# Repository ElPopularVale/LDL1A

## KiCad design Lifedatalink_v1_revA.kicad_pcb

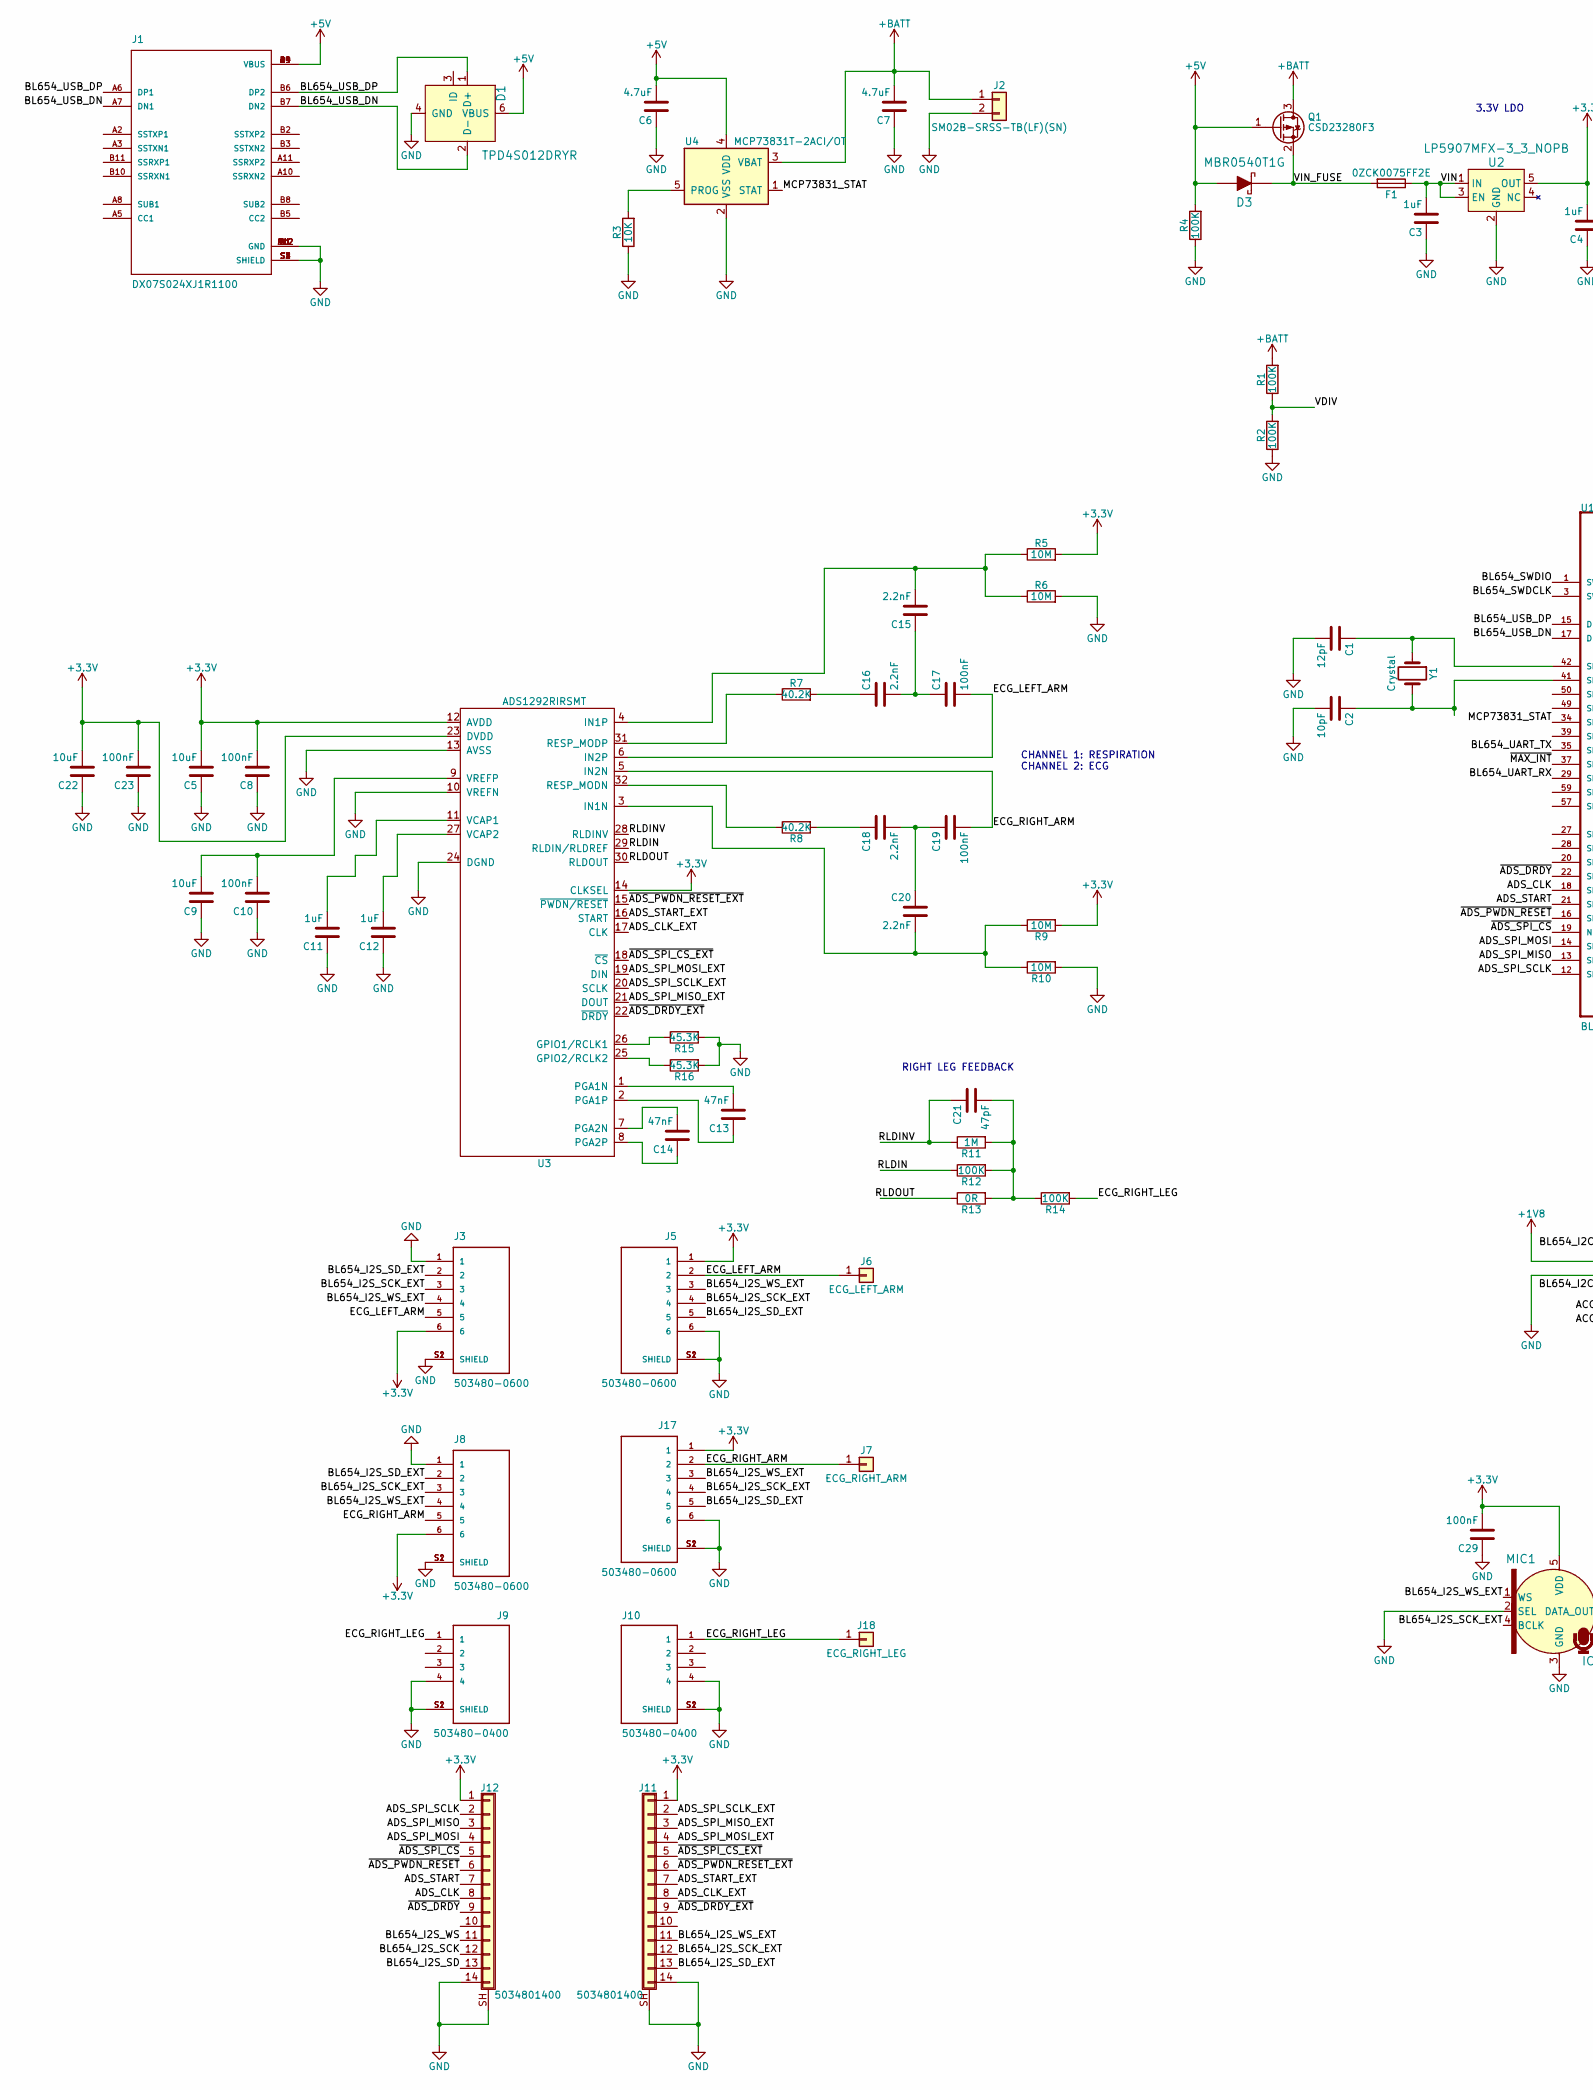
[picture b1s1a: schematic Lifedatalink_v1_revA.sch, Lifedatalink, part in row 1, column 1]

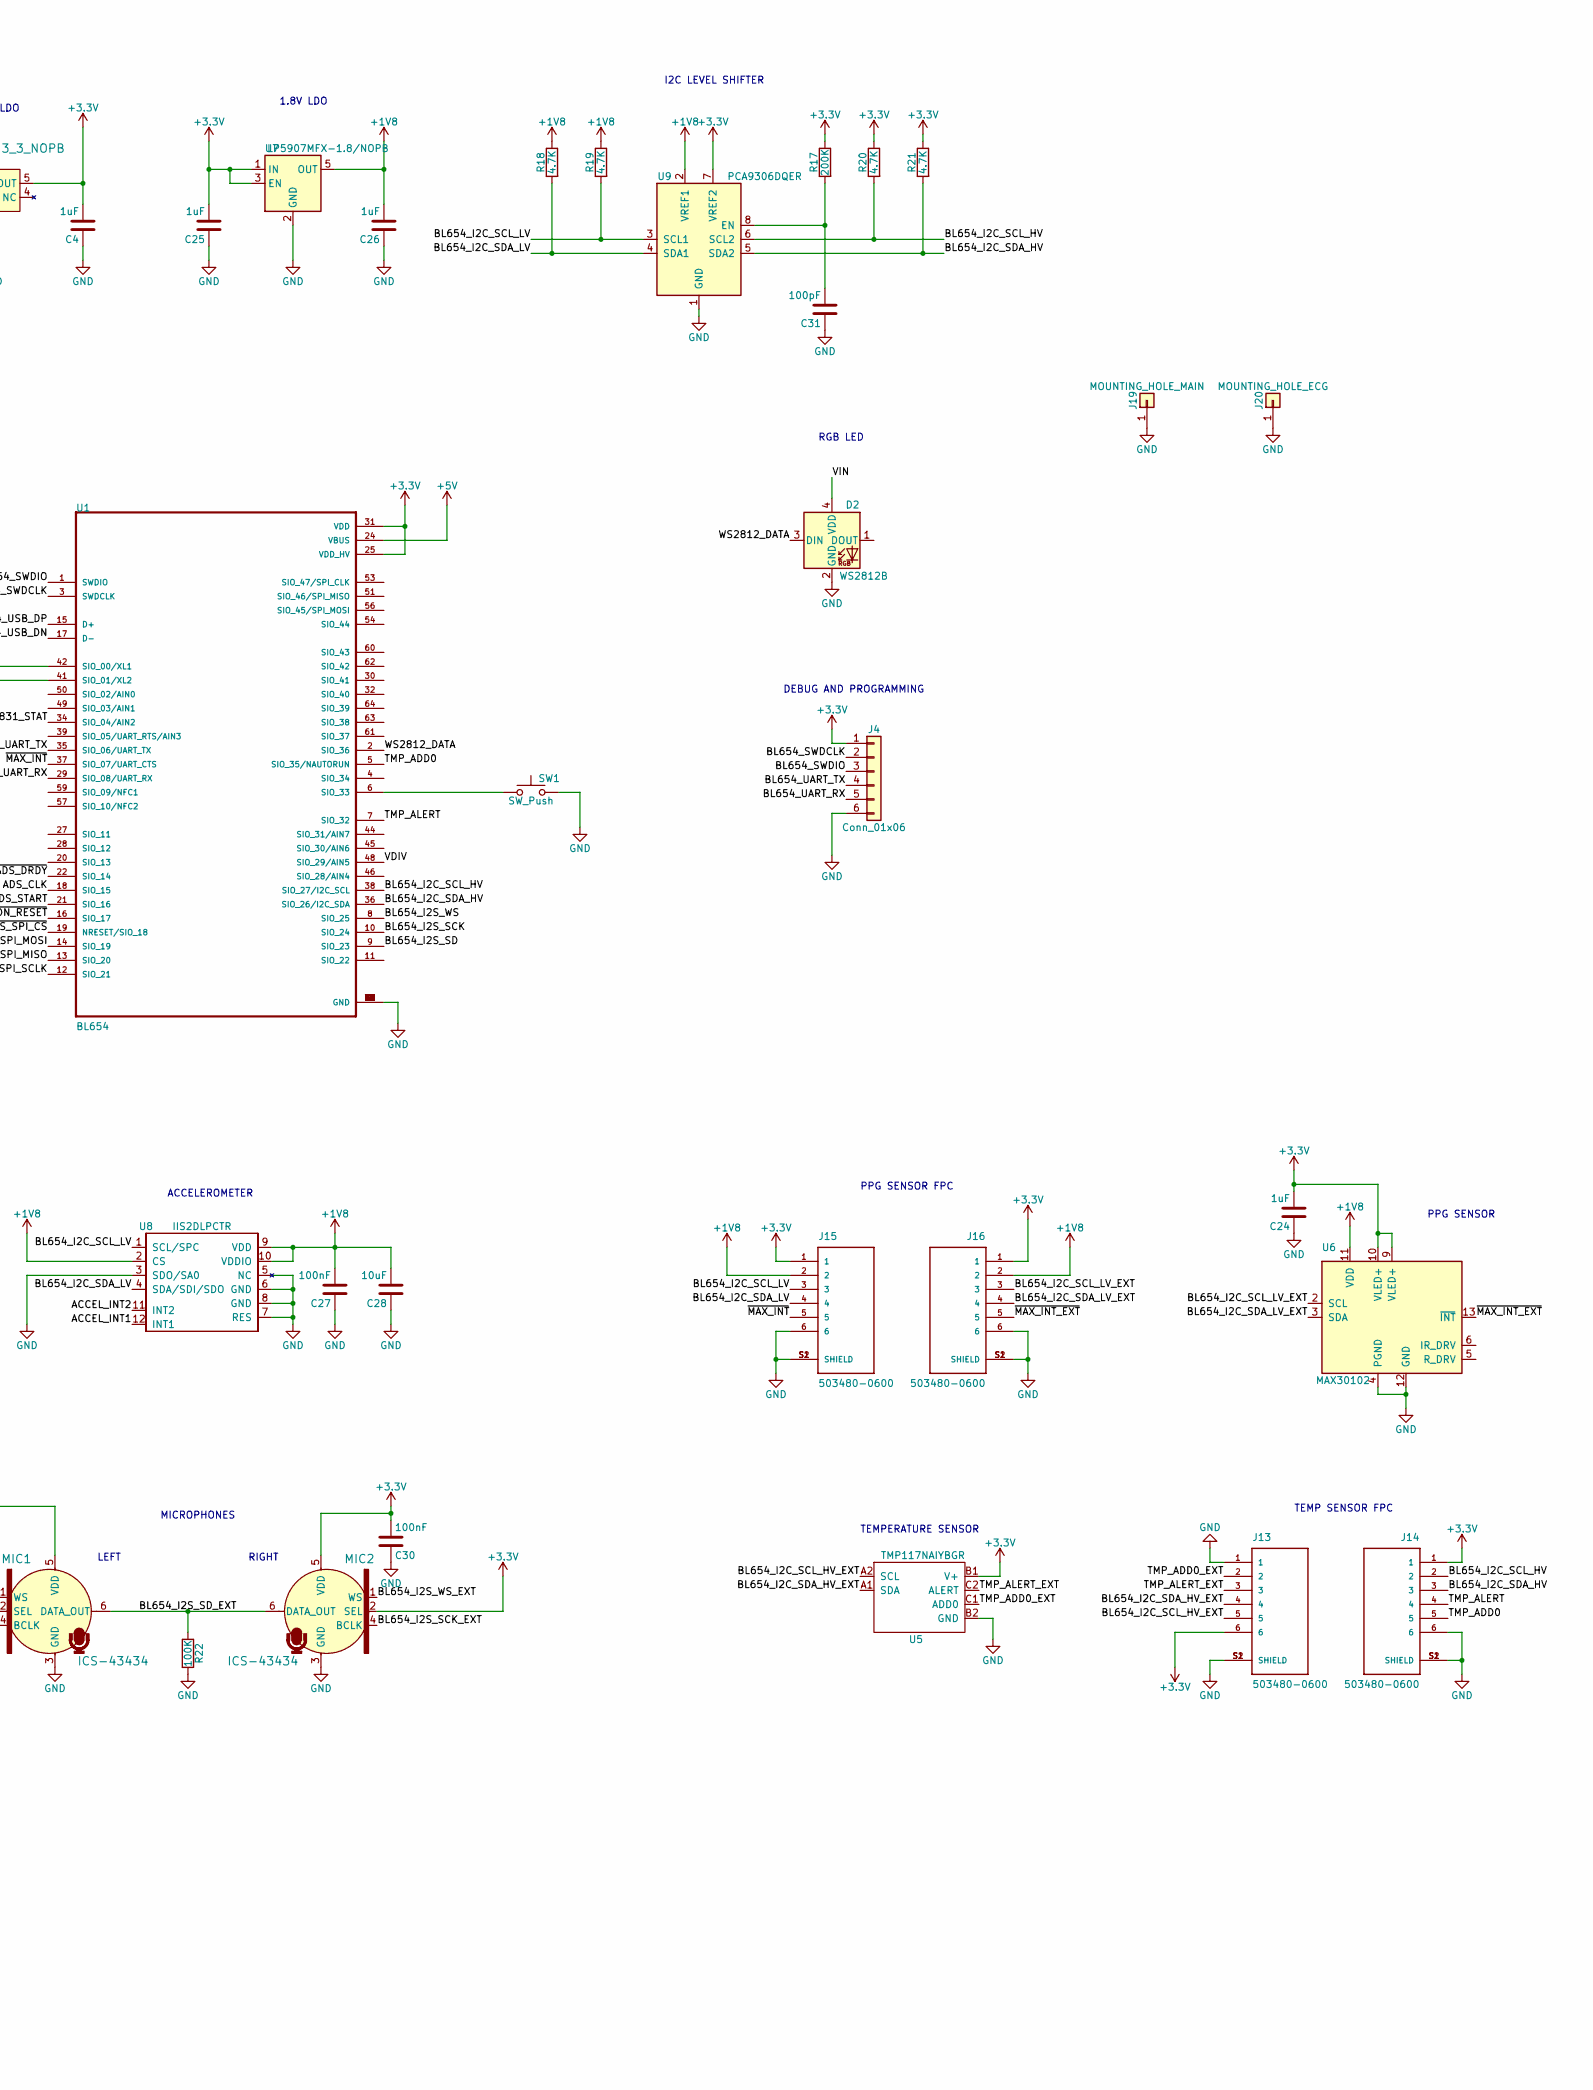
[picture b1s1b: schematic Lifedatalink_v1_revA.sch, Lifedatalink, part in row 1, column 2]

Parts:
C1: 12pF; C_0402_1005Metric; MPN C0402C120J5GACTU
C2: 10pF; C_0402_1005Metric; MPN C0402C100J5GACTU
C3, C4, C11, C12, C24, C25, C26: 1uF; C_0402_1005Metric; MPN C0402C105K9PACTU
C5, C9, C22, C28: 10uF; C_0402_1005Metric; MPN C0402C106M9PAC7867
C6, C7: 4.7uF; C_0402_1005Metric; MPN C0402C475M7PACTU
C8, C10, C17, C19, C23, C27, C29, C30: 100nF; C_0402_1005Metric; MPN C0402C104K4PACTU
C13, C14: 47nF; C_0402_1005Metric; MPN C0402C473K3RACAUTO
C15, C16, C18, C20: 2.2nF; C_0402_1005Metric; MPN C0402C222K5RACTU
C21: 47pF; C_0402_1005Metric; MPN C0402C470K5GACTU
C31: 100pF; C_0402_1005Metric; MPN C0402C101J5GACTU
D1: TPD4S012DRYR; SON50P100X145X60-6N; MPN TPD4S012DRYR; Digi-Key_PN 296-24244-1-ND
D2: WS2812B; LED_WS2812-2020; MPN APA-102-2020
D3: MBR0540T1G; D_SOD-123; MPN MBR0540T1G; Digi-Key_PN MBR0540T1GOSCT-ND
F1: 0ZCK0075FF2E; Fuse_0805_2012Metric; MPN 0603L075SLYR
J1: DX07S024XJ1R1100; JAE_DX07S024XJ1R1100; MPN DX07S024XJ1R1100
J2: SM02B-SRSS-TB(LF)(SN); JST_SH_SM02B-SRSS-TB_1x02-1MP_P1.00mm_Horizontal; MPN SM02B-SRSS-TB(LF)(SN)
J3, J5, J8, J13, J14, J15, J16, J17: 503480-0600; MOLEX_503480-0600; MPN 503480-0600
J4: Conn_01x06; 1.27mm_pads_01x06
J6: ECG_LEFT_ARM; ECG_SNAP
J7: ECG_RIGHT_ARM; ECG_SNAP
J9, J10: 503480-0400; MOLEX_503480-0400; MPN 503480-0400
J11, J12: 5034801400; MPN 503480-1400
J18: ECG_RIGHT_LEG; ECG_SNAP
J19: MOUNTING_HOLE_MAIN; MountingHole_2.2mm_M2_DIN965_Pad
J20: MOUNTING_HOLE_ECG; MountingHole_2.2mm_M2_DIN965_Pad
MIC1, MIC2: ICS-43434; SPH0645LM4H-B; MPN ICS-43434
Q1: CSD23280F3; TRANS_CSD23280F3; MPN CSD23280F3
R1, R2, R4, R12, R14, R22: 100K; R_0402_1005Metric; MPN CRCW0402100KFKEDC
R3: 10K; R_0402_1005Metric; MPN CRCW040210K0FKEDC
R5, R6, R9, R10: 10M; R_0402_1005Metric; MPN CRCW040210M0FKED
R7, R8: 40.2K; R_0402_1005Metric; MPN CRCW040240K2FKEDC
R11: 1M; R_0402_1005Metric; MPN CRCW04021M00FKEDC
R13: 0R; R_0402_1005Metric; MPN CRCW04020000Z0EDC
R15, R16: 45.3K; R_0402_1005Metric; MPN RC0402FR-0745K3L
R17: 200K; R_0402_1005Metric; MPN RC0402FR-07200KL
R18, R19, R20, R21: 4.7K; R_0402_1005Metric; MPN CRCW04024K70FKEDC
SW1: SW_Push; SW_B3U-3000P; MPN B3U-3000P
U1: BL654; XCVR_451-00001; MPN BL654
U2: LP5907MFX-3_3_NOPB; SOT-23-5; MPN LP5907MFX-3.3/NOPB; Digi-Key_PN 296-38557-1-ND
U3: ADS1292RIRSMT; QFN-32-1EP_4x4mm_P0.4mm_EP2.9x2.9mm; MPN ADS1292RIRSMT
U4: MCP73831T-2ACI/OT; SOT-23-5; MPN MCP73831T-2ACI/OT
U5: TMP117NAIYBGR; Texas_DSBGA-6_0.9x1.4mm_Layout2x3_P0.5mm; MPN TMP117NAIYBGR
U6: MAX30102; Maxim_OLGA-14_3.3x5.6mm_P0.8mm; MPN MAX30102EFD+
U7: LP5907MFX-1.8/NOPB; SOT-23-5; MPN LP5907MFX-1.8/NOPB
U8: IIS2DLPCTR; LGA-12_2x2mm_P0.5mm; MPN IIS2DLPCTR
U9: PCA9306DQER; X2SON-8_1.4x1mm_P0.35mm; MPN PCA9306DQER
Y1: Crystal; ABS05-32.768KHZ-T; MPN ABS05-32.768KHZ-9-T

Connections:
+1V8: C26.2, C27.2, C28.2, J15.2, J16.2, R18.1, R19.1, U6.11 (VDD), U7.5 (OUT), U8.2 (CS), U8.9 (VDD), U8.10 (VDDIO), U9.2 (VREF1)
+3V3: C4.2, C5.2, C8.2, C22.2, C23.2, C24.2, C25.2, C29.2, C30.2, J3.6, J4.1, J5.1, J8.6, J11.1, J12.1, J13.6, J14.1, J15.1, J16.1, J17.1, MIC1.5 (VDD), MIC2.2 (SEL), MIC2.5 (VDD), R5.2, R9.2, R17.1, R20.1, R21.1, U1.25 (VDD_HV), U1.31 (VDD), U2.5 (OUT), U3.12 (AVDD), U3.14 (CLKSEL), U3.23 (DVDD), U5.B1 (V+), U6.9 (VLED+), U6.10 (VLED+), U7.1 (IN), U7.3 (EN), U9.7 (VREF2)
+5V: C6.2, D1.6 (VBUS), D3.2, D3.A, J1.A4 (VBUS), J1.A9 (VBUS), J1.B4 (VBUS), J1.B9 (VBUS), Q1.1 (G), R4.2, U1.24 (VBUS), U4.4 (VDD)
+BATT: C7.2, J2.1, Q1.3 (D), R1.2, U4.3 (VBAT)
/ACCEL_INT1: U8.12 (INT1)
/ACCEL_INT2: U8.11 (INT2)
/ADS_CLK: J12.8, U1.18 (SIO_15)
/ADS_CLK_EXT: J11.8, U3.17 (CLK)
/ADS_SPI_MISO: J12.3, U1.13 (SIO_20)
/ADS_SPI_MISO_EXT: J11.3, U3.21 (DOUT)
/ADS_SPI_MOSI: J12.4, U1.14 (SIO_19)
/ADS_SPI_MOSI_EXT: J11.4, U3.19 (DIN)
/ADS_SPI_SCLK: J12.2, U1.12 (SIO_21)
/ADS_SPI_SCLK_EXT: J11.2, U3.20 (SCLK)
/ADS_START: J12.7, U1.21 (SIO_16)
/ADS_START_EXT: J11.7, U3.16 (START)
/BL654_I2C_SCL_HV: J14.2, R20.2, U1.38 (SIO_27/I2C_SCL), U9.6 (SCL2)
/BL654_I2C_SCL_HV_EXT: J13.5, U5.A2 (SCL)
/BL654_I2C_SCL_LV: J15.3, R19.2, U8.1 (SCL/SPC), U9.3 (SCL1)
/BL654_I2C_SCL_LV_EXT: J16.3, U6.2 (SCL)
/BL654_I2C_SDA_HV: J14.3, R21.2, U1.36 (SIO_26/I2C_SDA), U9.5 (SDA2)
/BL654_I2C_SDA_HV_EXT: J13.4, U5.A1 (SDA)
/BL654_I2C_SDA_LV: J15.4, R18.2, U8.4 (SDA/SDI/SDO), U9.4 (SDA1)
/BL654_I2C_SDA_LV_EXT: J16.4, U6.3 (SDA)
/BL654_I2S_SCK: J12.12, U1.10 (SIO_24)
/BL654_I2S_SCK_EXT: J3.3, J5.4, J8.3, J11.12, J17.4, MIC1.4 (BCLK), MIC2.4 (BCLK)
/BL654_I2S_SD: J12.13, U1.9 (SIO_23)
/BL654_I2S_SD_EXT: J3.2, J5.5, J8.2, J11.13, J17.5, MIC1.6 (DATA_OUT), MIC2.6 (DATA_OUT), R22.1
/BL654_I2S_WS: J12.11, U1.8 (SIO_25)
/BL654_I2S_WS_EXT: J3.4, J5.3, J8.4, J11.11, J17.3, MIC1.1 (WS), MIC2.1 (WS)
/BL654_SWDCLK: J4.2, U1.3 (SWDCLK)
/BL654_SWDIO: J4.3, U1.1 (SWDIO)
/BL654_UART_RX: J4.5, U1.29 (SIO_08/UART_RX)
/BL654_UART_TX: J4.4, U1.35 (SIO_06/UART_TX)
/BL654_USB_DN: D1.2 (D-), J1.A7 (DN1), J1.B7 (DN2), U1.17 (D-)
/BL654_USB_DP: D1.1 (D+), J1.A6 (DP1), J1.B6 (DP2), U1.15 (D+)
/ECG_LEFT_ARM: C17.2, J3.5, J5.2, J6.1, U3.6 (IN2P)
/ECG_RIGHT_ARM: C19.2, J7.1, J8.5, J17.2, U3.5 (IN2N)
/ECG_RIGHT_LEG: J9.1, J10.1, J18.1, R14.2
/MCP73831_STAT: U1.34 (SIO_04/AIN2), U4.1 (STAT)
/RLDIN: R12.1, U3.29 (RLDIN/RLDREF)
/RLDINV: C21.1, R11.1, U3.28 (RLDINV)
/RLDOUT: R13.1, U3.30 (RLDOUT)
/TMP_ADD0: J14.5, U1.5 (SIO_35/NAUTORUN)
/TMP_ADD0_EXT: J13.2, U5.C1 (ADD0)
/TMP_ALERT: J14.4, U1.7 (SIO_32)
/TMP_ALERT_EXT: J13.3, U5.C2 (ALERT)
/VDIV: R1.1, R2.2, U1.48 (SIO_29/AIN5)
/VIN: C3.2, D2.4 (VDD), F1.1, U2.1 (IN), U2.3 (EN)
/VIN_FUSE: D3.1, D3.K, F1.2, Q1.2 (S)
/WS2812_DATA: D2.3 (DIN), U1.2 (SIO_36)
/~ADS_DRDY: J12.9, U1.22 (SIO_14)
/~ADS_DRDY_EXT: J11.9, U3.22 (~DRDY)
/~ADS_PWDN_RESET: J12.6, U1.16 (SIO_17)
/~ADS_PWDN_RESET_EXT: J11.6, U3.15 (~PWDN/RESET)
/~ADS_SPI_CS: J12.5, U1.19 (NRESET/SIO_18)
/~ADS_SPI_CS_EXT: J11.5, U3.18 (~CS)
/~MAX_INT: J15.5, U1.37 (SIO_07/UART_CTS)
/~MAX_INT_EXT: J16.5, U6.13 (~INT)
GND: C1.2, C2.2, C3.1, C4.1, C5.1, C6.1, C7.1, C8.1, C9.1, C10.1, C11.1, C12.1, C22.1, C23.1, C24.1, C25.1, C26.1, C27.1, C28.1, C29.1, C30.1, C31.1, D1.4 (GND), D2.2 (GND), J1.A1 (GND), J1.A12 (GND), J1.B1 (GND), J1.B12 (GND), J1.S1 (SHIELD), J1.S2 (SHIELD), J1.S3 (SHIELD), J1.S4 (SHIELD), J2.2, J3.1, J3.S1 (SHIELD), J3.S2 (SHIELD), J4.6, J5.6, J5.S1 (SHIELD), J5.S2 (SHIELD), J8.1, J8.S1 (SHIELD), J8.S2 (SHIELD), J9.4, J9.S1 (SHIELD), J9.S2 (SHIELD), J10.4, J10.S1 (SHIELD), J10.S2 (SHIELD), J11.14, J11.SH (Shield), J12.14, J12.SH (Shield), J13.1, J13.S1 (SHIELD), J13.S2 (SHIELD), J14.6, J14.S1 (SHIELD), J14.S2 (SHIELD), J15.6, J15.S1 (SHIELD), J15.S2 (SHIELD), J16.6, J16.S1 (SHIELD), J16.S2 (SHIELD), J17.6, J17.S1 (SHIELD), J17.S2 (SHIELD), J19.1, J20.1, MIC1.2 (SEL), MIC1.3 (GND), MIC2.3 (GND), R2.1, R3.1, R4.1, R6.2, R10.2, R15.2, R16.2, R22.2, SW1.2, U1.0 (GND), U1.23 (GND), U1.26 (GND), U1.33 (GND), U1.40 (GND), U1.43 (GND), U1.47 (GND), U1.52 (GND), U1.55 (GND), U1.58 (GND), U1.65 (GND), U1.66 (GND), U1.67 (GND), U1.68 (GND), U1.69 (GND), U1.70 (GND), U1.71 (GND), U2.2 (GND), U3.10 (VREFN), U3.13 (AVSS), U3.24 (DGND), U4.2 (VSS), U5.B2 (GND), U6.4 (PGND), U6.12 (GND), U7.2 (GND), U8.3 (SDO/SA0), U8.5 (NC), U8.6 (GND), U8.7 (RES), U8.8 (GND), U9.1 (GND)
unnamed: C1.1, U1.42 (SIO_00/XL1), Y1.1
unnamed: C2.1, U1.41 (SIO_01/XL2), Y1.2
unnamed: C9.2, C10.2, U3.9 (VREFP)
unnamed: C11.2, U3.11 (VCAP1)
unnamed: C12.2, U3.27 (VCAP2)
unnamed: C13.1, U3.2 (PGA1P)
unnamed: C13.2, U3.1 (PGA1N)
unnamed: C14.1, U3.8 (PGA2P)
unnamed: C14.2, U3.7 (PGA2N)
unnamed: C15.1, C16.2, C17.1
unnamed: C15.2, R5.1, R6.1, U3.4 (IN1P)
unnamed: C16.1, R7.2
unnamed: C18.1, R8.2
unnamed: C18.2, C19.1, C20.1
unnamed: C20.2, R9.1, R10.1, U3.3 (IN1N)
unnamed: C21.2, R11.2, R12.2, R13.2, R14.1
unnamed: C31.2, R17.2, U9.8 (EN)
unnamed: R3.2, U4.5 (PROG)
unnamed: R7.1, U3.31 (RESP_MODP)
unnamed: R8.1, U3.32 (RESP_MODN)
unnamed: R15.1, U3.26 (GPIO1/RCLK1)
unnamed: R16.1, U3.25 (GPIO2/RCLK2)
unnamed: SW1.1, U1.6 (SIO_33)

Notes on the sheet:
RIGHT LEG FEEDBACK
CHANNEL 1: RESPIRATION CHANNEL 2: ECG
TEMPERATURE SENSOR
DEBUG AND PROGRAMMING
PPG SENSOR
I2C LEVEL SHIFTER
1.8V LDO
3.3V LDO
LEFT
RIGHT
RGB LED
PPG SENSOR FPC
ACCELEROMETER
MICROPHONES
TEMP SENSOR FPC

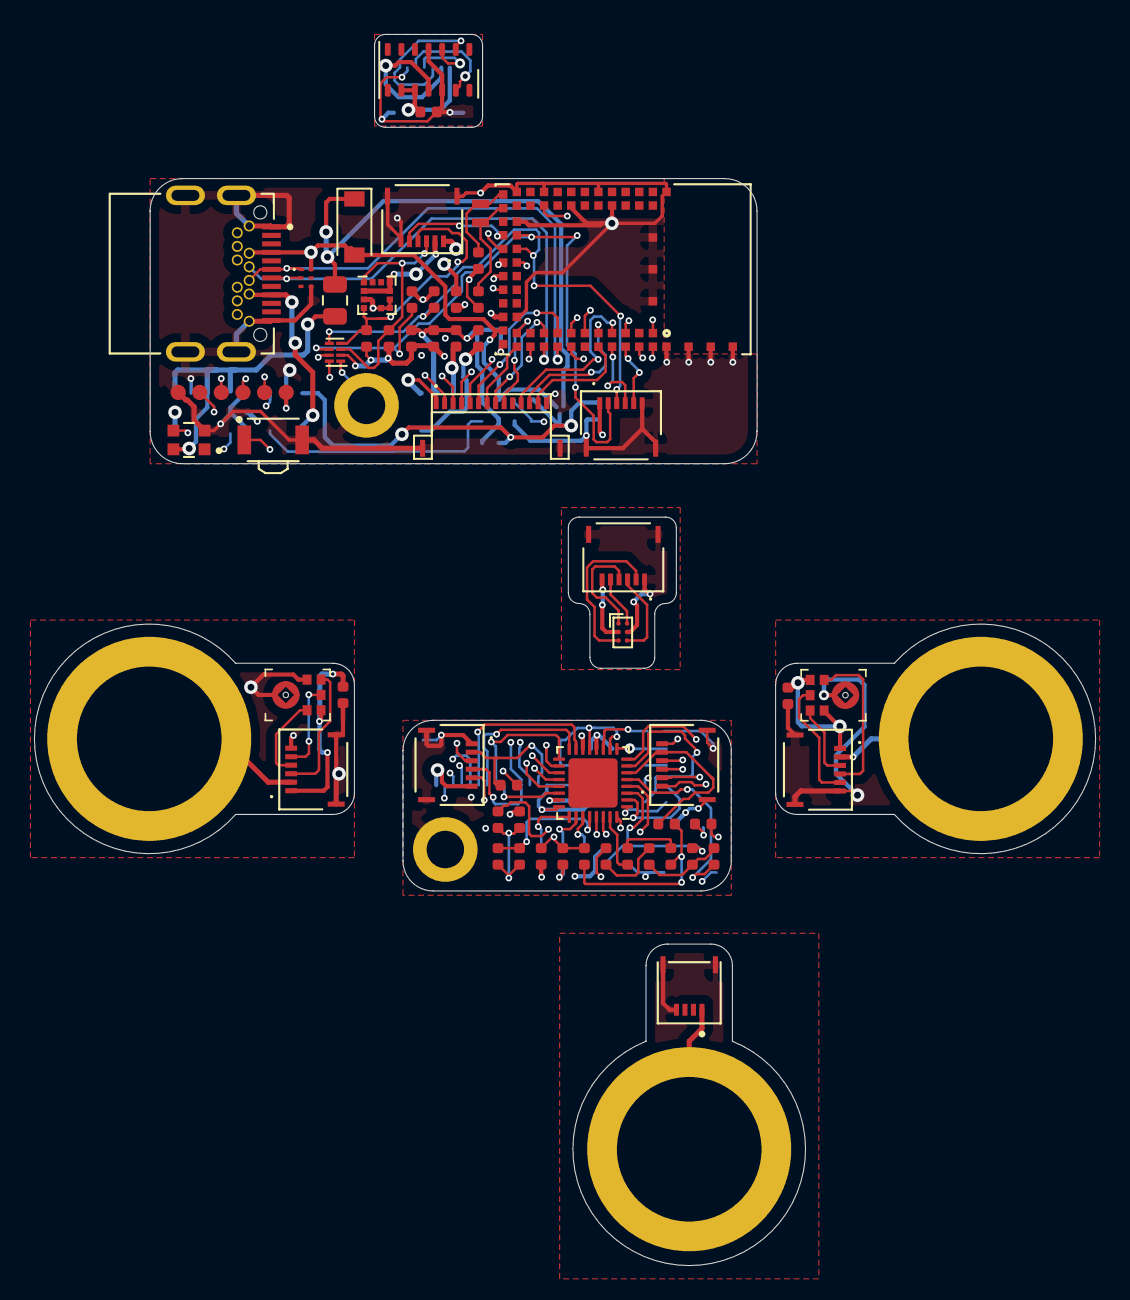
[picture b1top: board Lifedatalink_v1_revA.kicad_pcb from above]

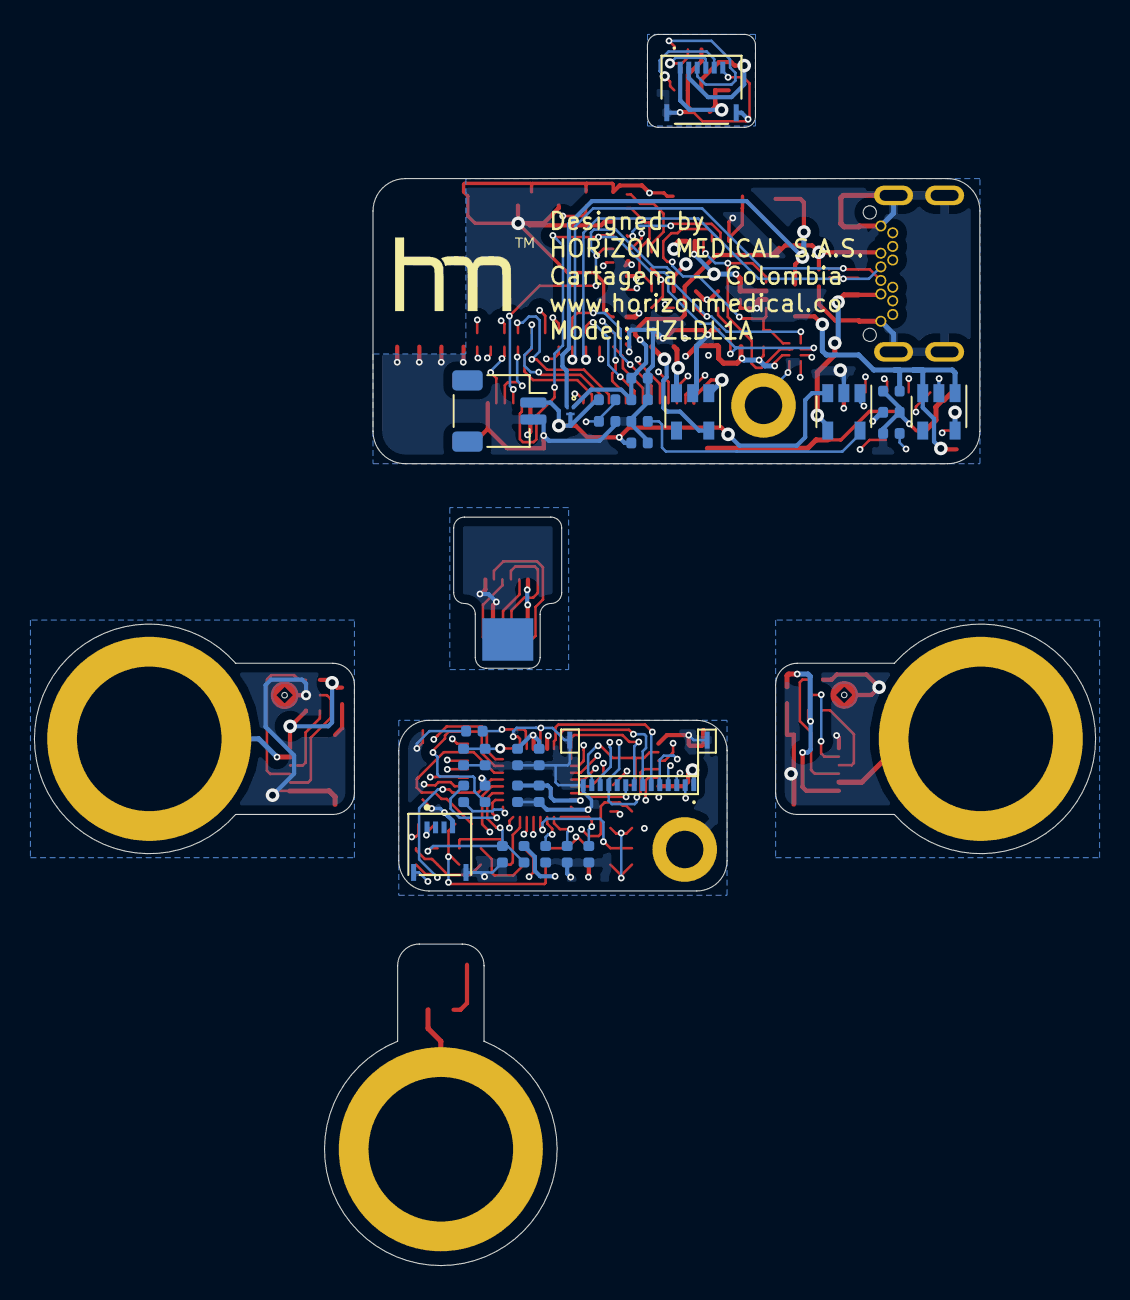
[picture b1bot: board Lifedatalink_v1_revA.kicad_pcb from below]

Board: 4 copper layers, 62.4 x 72.4 mm, 92 parts (32 on the bottom side), 81 nets.

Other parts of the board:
P6: HORIZON MEDICAL LOGO; horizon_logo_silk_small

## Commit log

2020-03-28 Hexagonal PCB placed
2020-03-29 Cutted PCB placed and 3D models added
2020-03-31 Added ECG snaps, microphones and other 3D models.
2020-04-01 Fixed LED and added JST connector to battery plus more 3D models
2020-04-01 Changed layout and added button
2020-04-04 Added board properties
2020-04-07 Main board routed
2020-04-09 Completed routing of all boards
2020-04-15 Fix temperature sensor thermal pad, mounting holes, silk screen, mic ground, capacitor symmetric location and routing
2020-04-19 Finished post routing schematic pinout and footprint cross check
2020-04-20 Added battery level voltage divider
2020-04-22 Changed the color of FFC connectors
2020-04-22 Fixed electrode boards
2020-04-22 Fixed small routing traces
2020-04-26 Finalized and exported CAD files for quotation
2020-04-30 Finalized and exported CAD for manufacturing including Fab layers
2020-05-19 Upgraded to Kicad nightly and exported schematic to Hackster.io contest
2020-05-19 Add README
2020-07-07 Add XY positioning file
2020-07-07 Add gitignore
2020-07-07 Add battery 3D model
